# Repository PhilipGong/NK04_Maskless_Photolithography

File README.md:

# NK04_Maskless_Photolithography
Project repository for developing an LCOS based maskless photolithography process.

---
## Objective
To develope an optical setup which is able to:
- Achieve <= 1um feature size
- Ability to expose photoresists at wavelength (405nm / 465nm)
- (Optional) Step the substrate for wafer stepping
- (Optional) Make use of the phase-shift ability of LCOS for phase shift masking

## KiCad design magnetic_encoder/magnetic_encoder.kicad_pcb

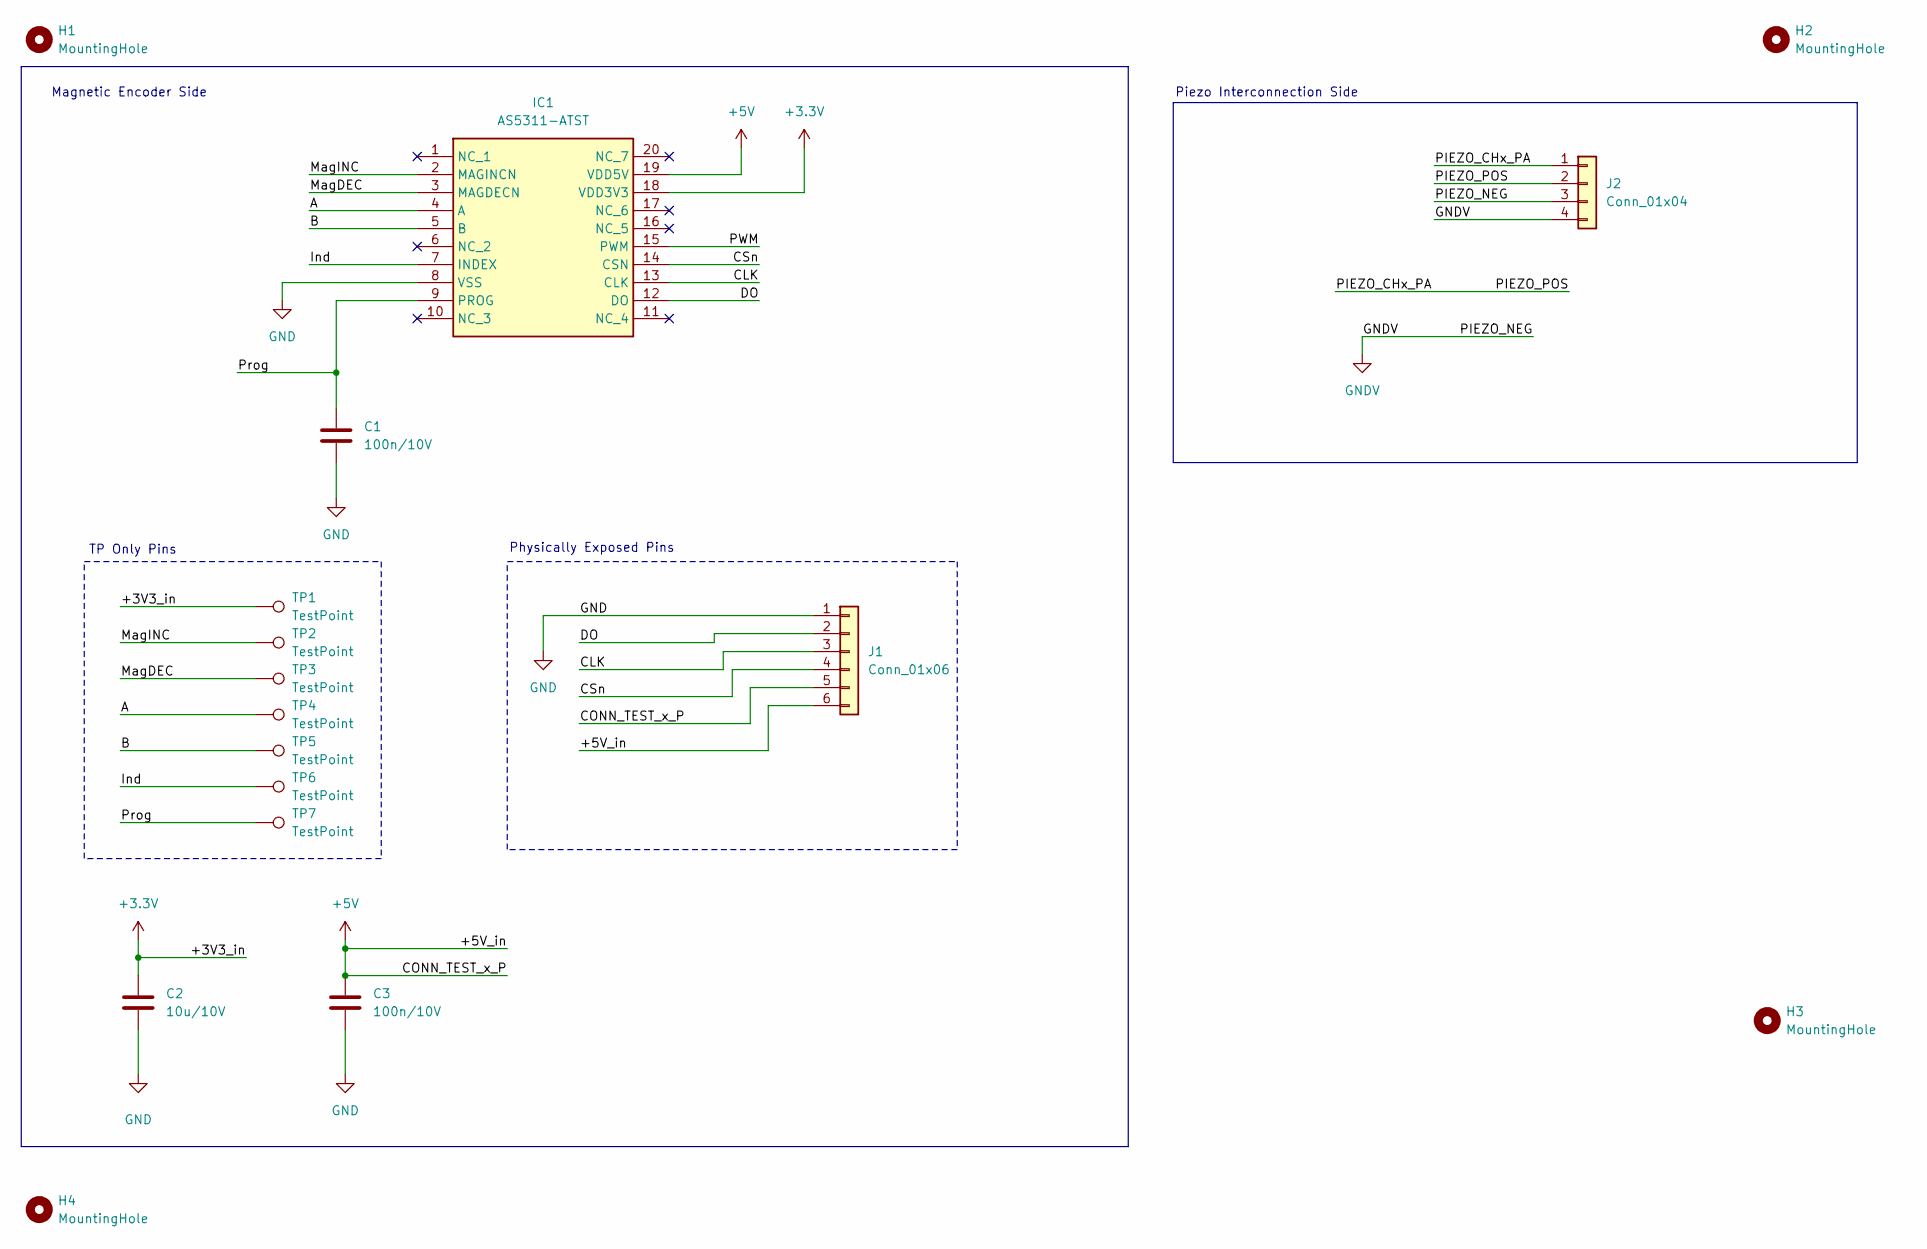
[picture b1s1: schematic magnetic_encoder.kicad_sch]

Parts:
C1, C3: 100n/10V; C_0805_2012Metric
C2: 10u/10V; C_0805_2012Metric
H1, H2, H3, H4: MountingHole; MountingHole_3.2mm_M3
IC1: AS5311-ATST; SOP65P640X120-20N; Manufacturer_Part_Number AS5311-ATST; Mouser Part Number 985-AS5311-ATST
J1: Conn_01x06; SolderWire-0.5sqmm_1x06_P4.6mm_D0.9mm_OD2.1mm_Relief
J2: Conn_01x04; SolderWire-0.5sqmm_1x04_P4.6mm_D0.9mm_OD2.1mm_Relief
TP1, TP2, TP3, TP4, TP5, TP6, TP7: TestPoint; TestPoint_Pad_D1.0mm

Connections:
+3.3V: C2.1, IC1.18 (VDD3V3), TP1.1
+5V: C3.1, IC1.19 (VDD5V), J1.5, J1.6
/A: IC1.4 (A), TP4.1
/B: IC1.5 (B), TP5.1
/CLK: IC1.13 (CLK), J1.3
/CSn: IC1.14 (CSN), J1.4
/DO: IC1.12 (DO), J1.2
/Ind: IC1.7 (INDEX), TP6.1
/MagDEC: IC1.3 (MAGDECN), TP3.1
/MagINC: IC1.2 (MAGINCN), TP2.1
/PIEZO_CHx_PA: J2.1, J2.2
/PWM: IC1.15 (PWM)
/Prog: C1.1, IC1.9 (PROG), TP7.1
GND: C1.2, C2.2, C3.2, IC1.8 (VSS), J1.1
GNDV: J2.3, J2.4

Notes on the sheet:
Physically Exposed Pins
Piezo Interconnection Side
Magnetic Encoder Side
TP Only Pins

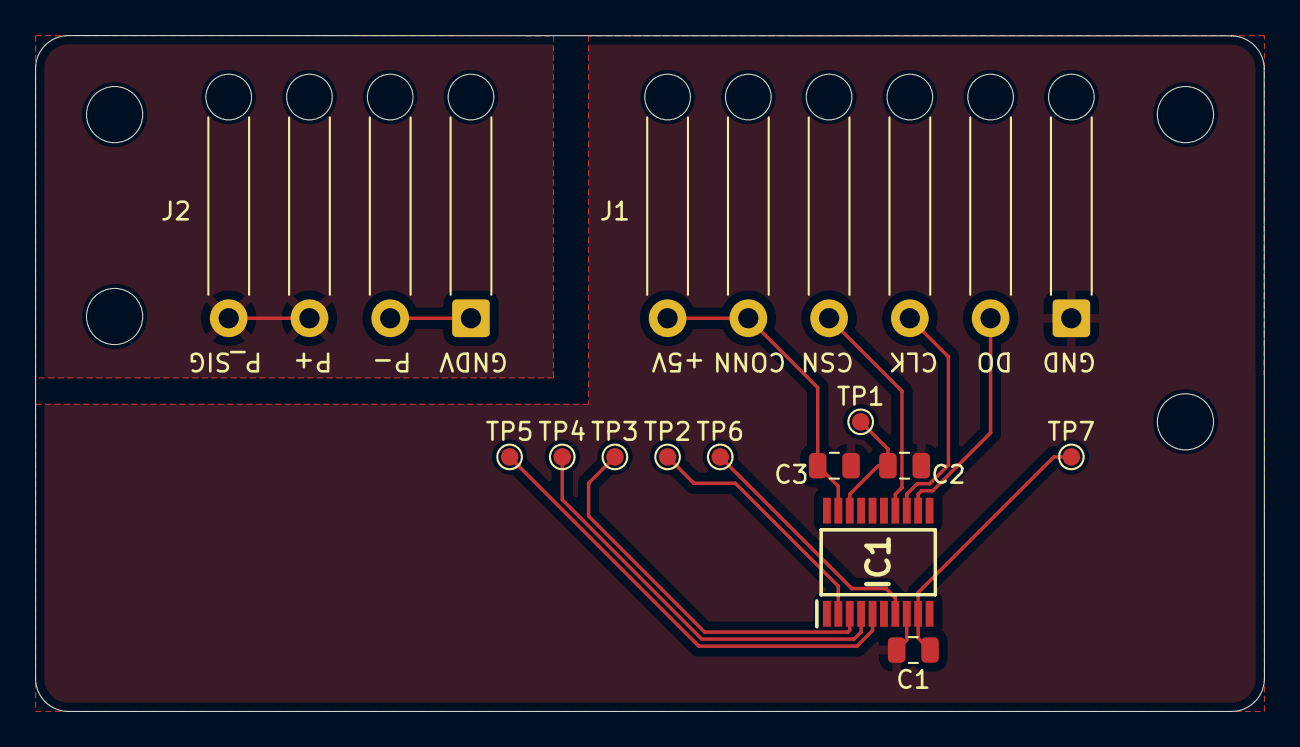
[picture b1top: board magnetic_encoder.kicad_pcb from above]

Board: 2 copper layers, 70.0 x 38.5 mm, 17 parts (0 on the bottom side), 14 nets.

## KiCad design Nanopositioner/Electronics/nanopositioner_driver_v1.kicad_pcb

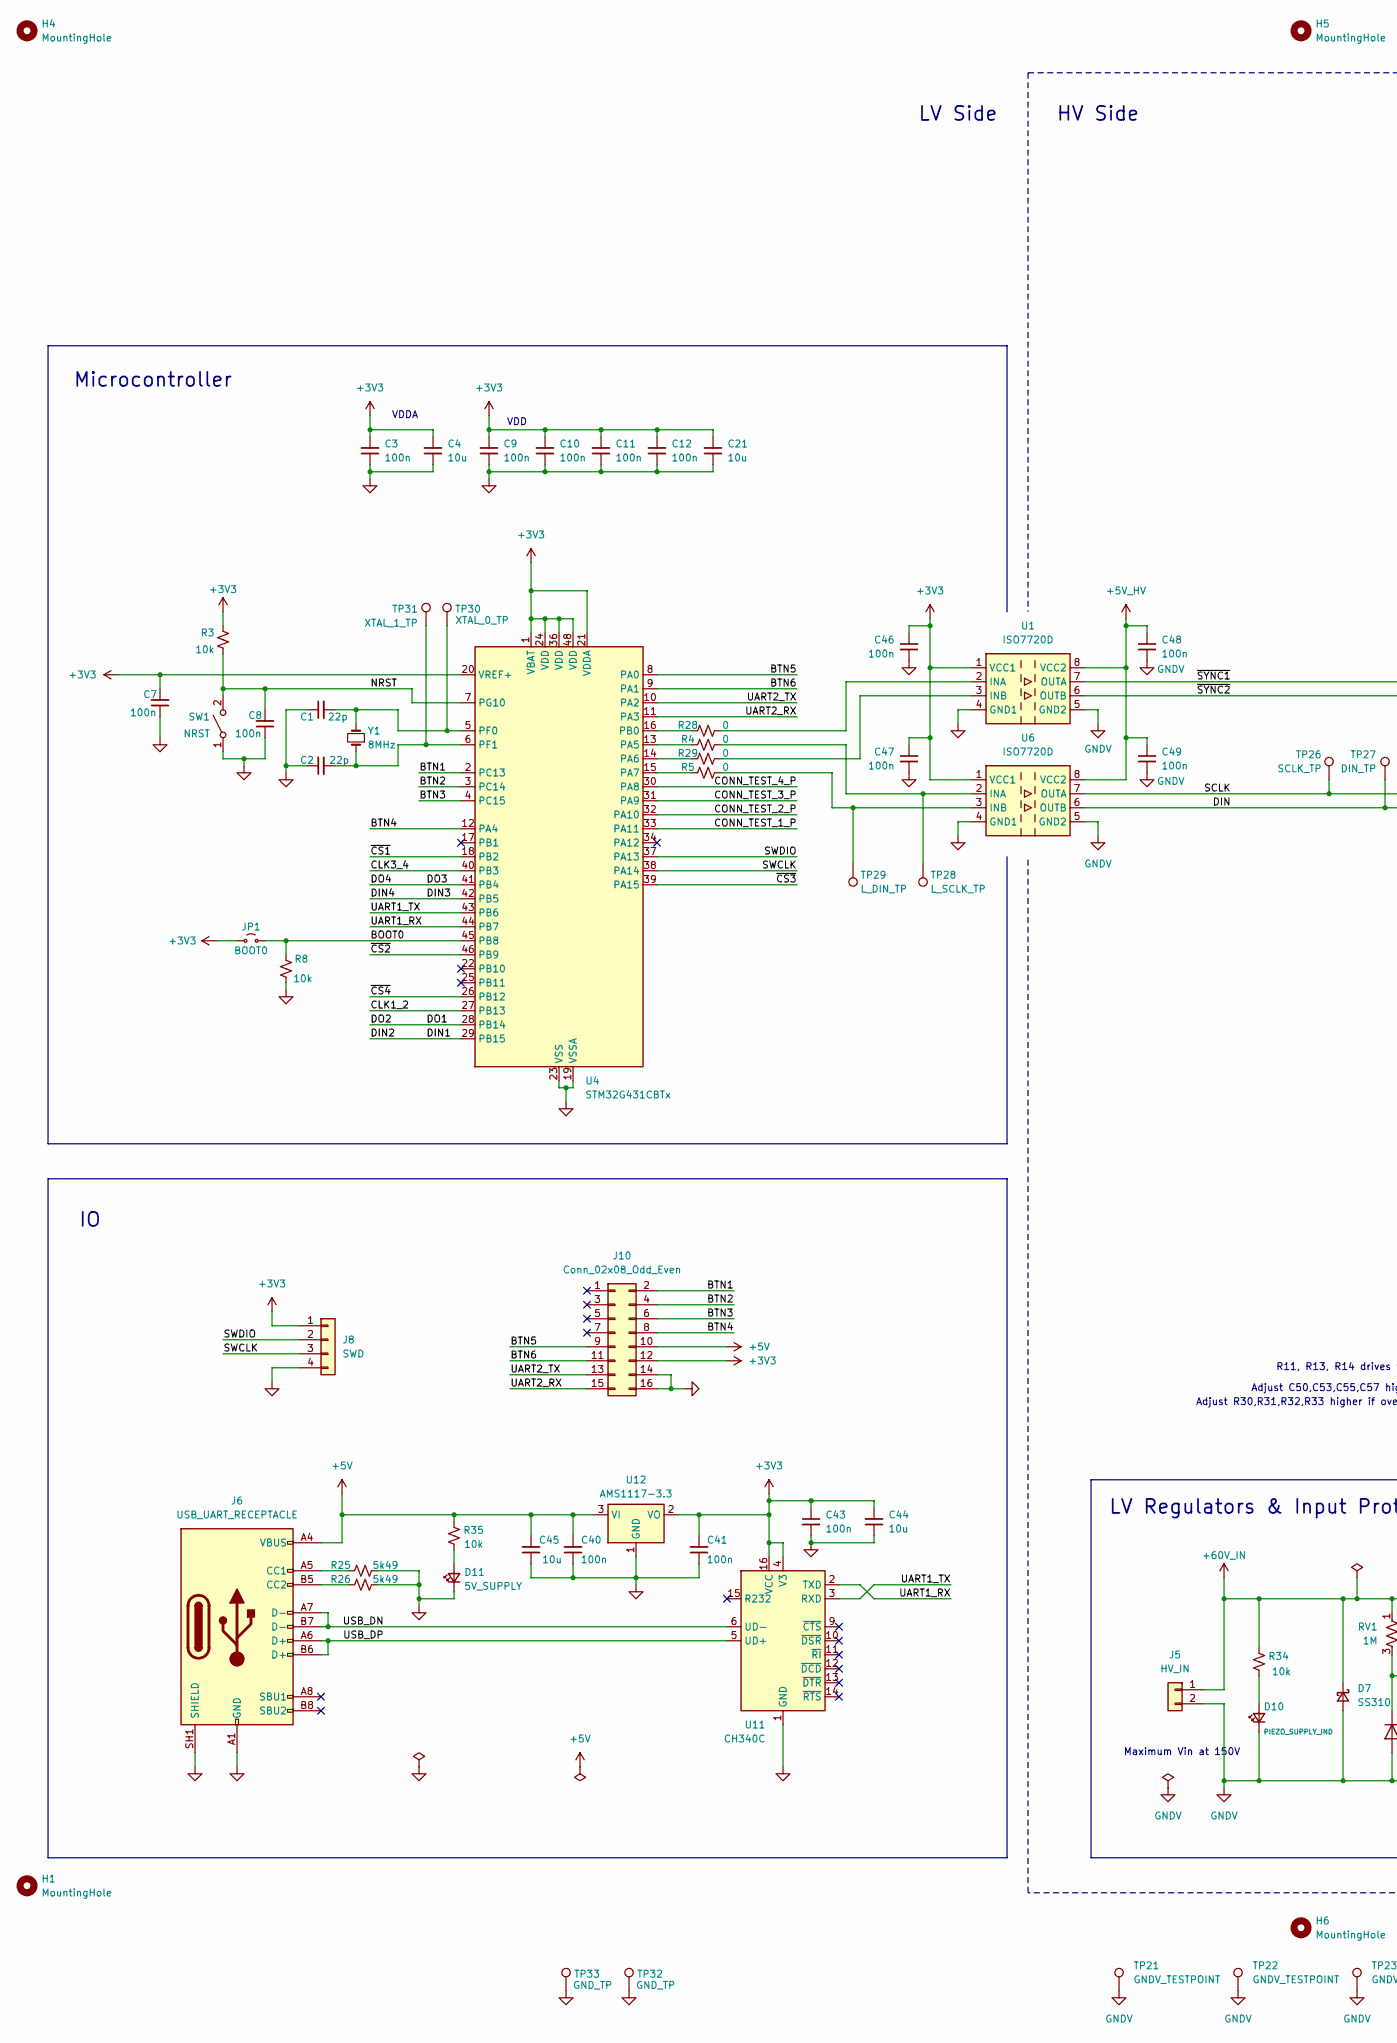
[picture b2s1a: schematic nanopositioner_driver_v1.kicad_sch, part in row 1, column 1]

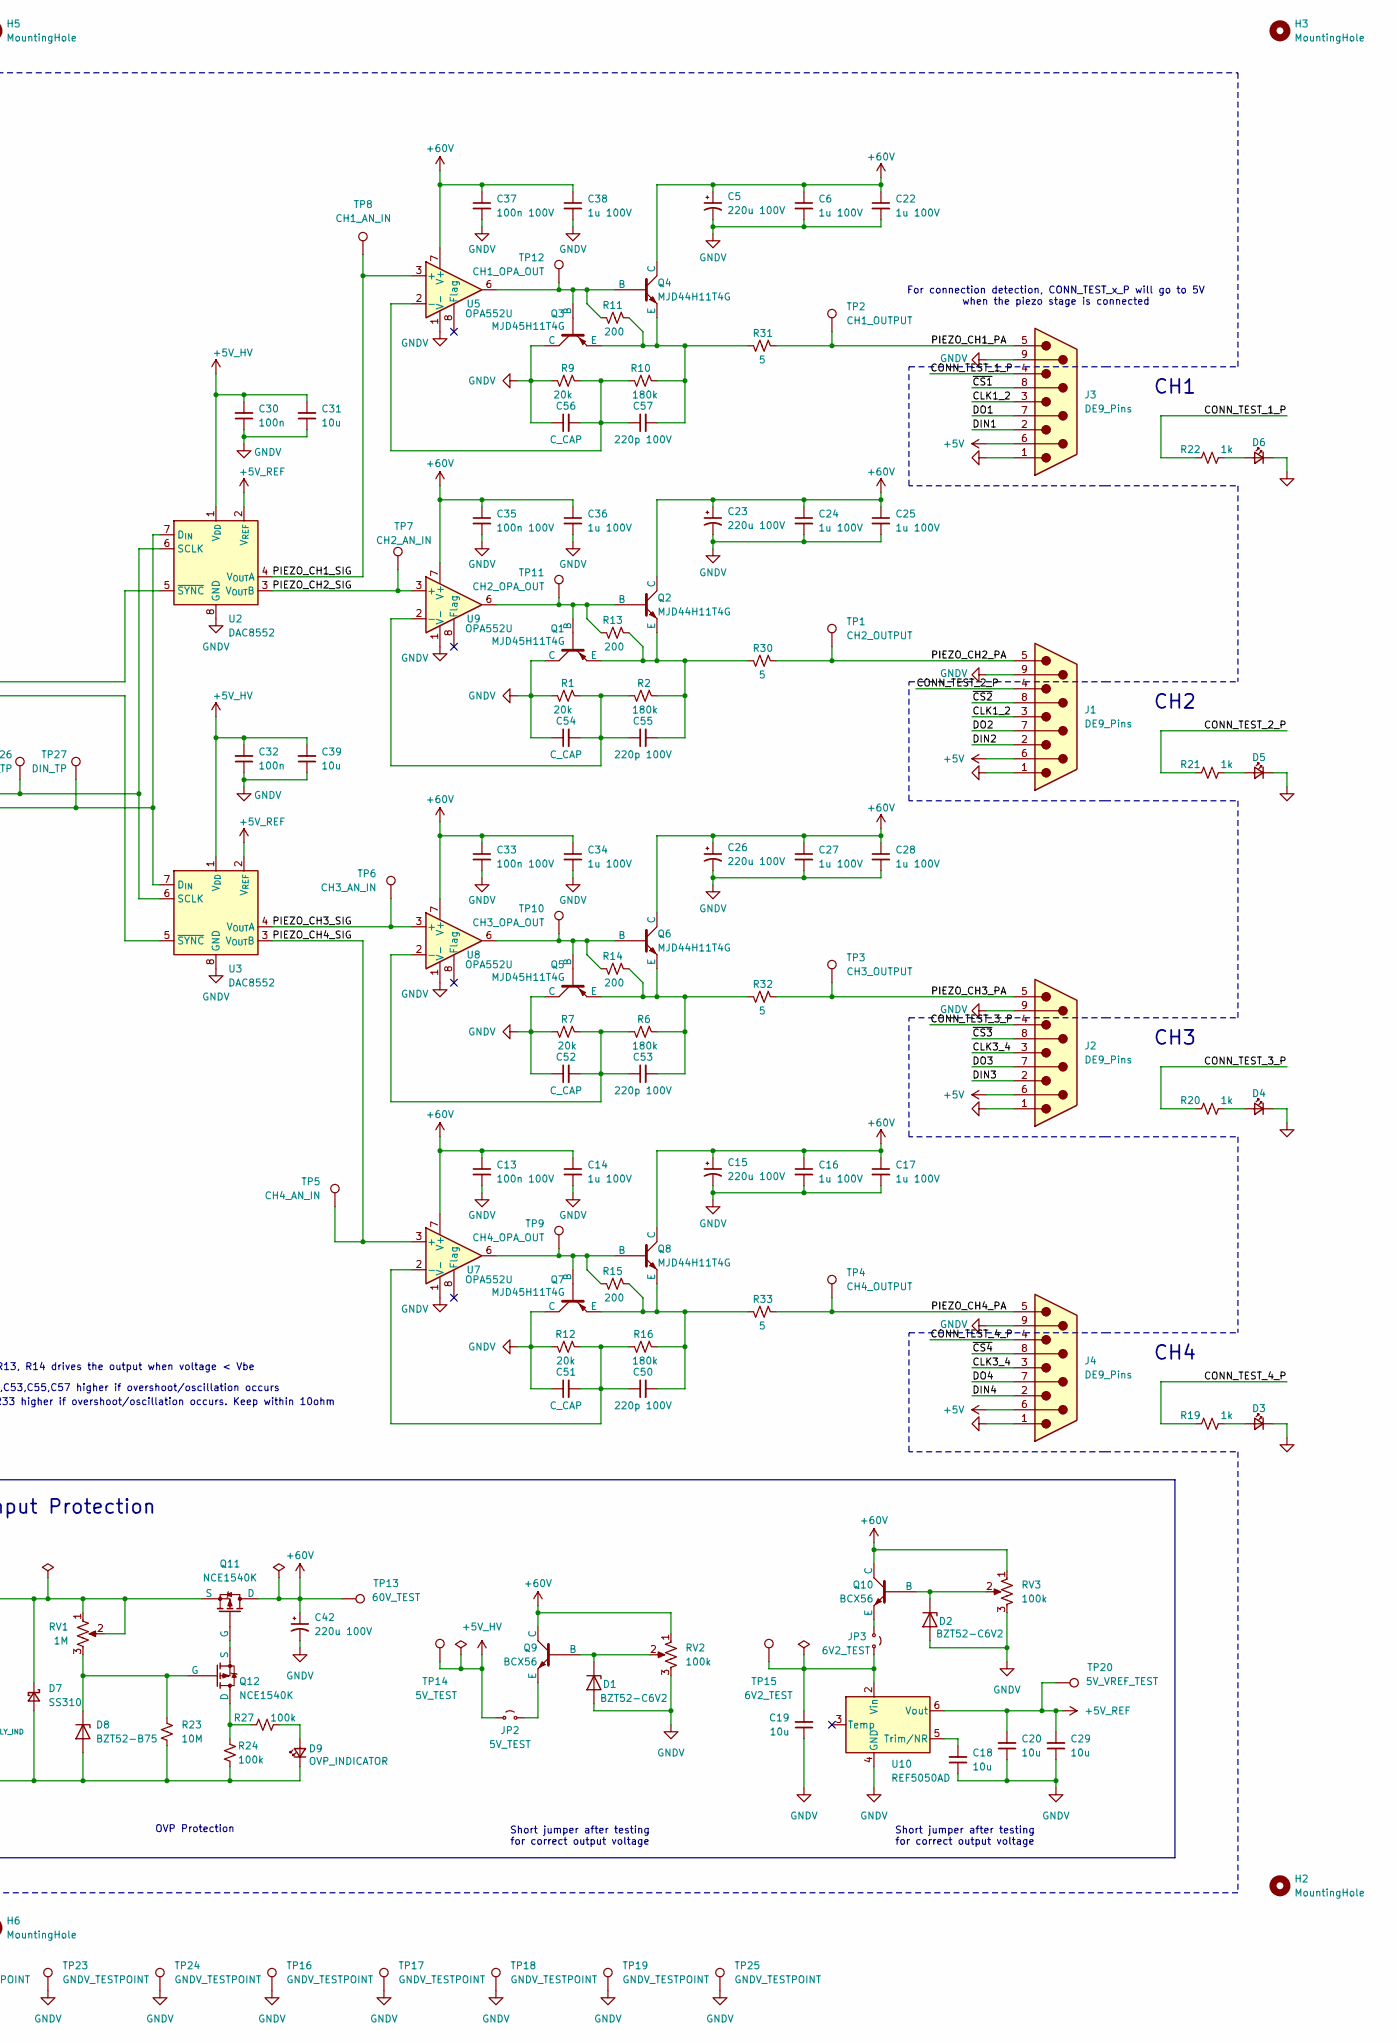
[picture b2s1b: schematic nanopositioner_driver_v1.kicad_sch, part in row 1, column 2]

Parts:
C1, C2: 22p; C_0603_1608Metric
C3, C7, C8, C9, C10, C11, C12, C30, C32, C40, C41, C43, C46, C47, C48, C49: 100n; C_0805_2012Metric
C4, C18, C19, C20, C21, C29, C31, C39, C44, C45: 10u; C_0805_2012Metric
C5, C15, C23, C26, C42: 220u 100V; CP_Radial_D13.0mm_P5.00mm
C6, C14, C16, C17, C22, C24, C25, C27, C28, C34, C36, C38: 1u 100V; C_1206_3216Metric
C13, C33, C35, C37: 100n 100V; C_0805_2012Metric
C50, C53, C55, C57: 220p 100V; C_1206_3216Metric
C51, C52, C54, C56: C_CAP; C_0805_2012Metric
D1, D2: BZT52-C6V2; D_SOD-123F
D3, D4, D5, D6: LED_Small; JST_XH_B2B-XH-A_1x02_P2.50mm_Vertical
D7: SS310; D_SMB
D8: BZT52-B75; D_SOD-123F
D9: OVP_INDICATOR; JST_XH_B2B-XH-A_1x02_P2.50mm_Vertical
D10: PIEZO_SUPPLY_IND; JST_XH_B2B-XH-A_1x02_P2.50mm_Vertical
D11: 5V_SUPPLY; JST_XH_B2B-XH-A_1x02_P2.50mm_Vertical
H1, H2, H3, H4, H5, H6: MountingHole; MountingHole_3.2mm_M3
J1, J2, J3, J4: DE9_Pins; DSUB-9_Socket_Horizontal_P2.77x2.84mm_EdgePinOffset7.70mm_H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
J5: HV_IN; TerminalBlock_bornier-2_P5.08mm
J6: USB_UART_RECEPTACLE; GCT_USB4105GFA120
J8: SWD; PinSocket_1x04_P2.54mm_Vertical
J10: Conn_02x08_Odd_Even; PinHeader_2x08_P2.54mm_Vertical
JP1: BOOT0; PinHeader_1x02_P2.54mm_Vertical
JP2: 5V_TEST; SolderJumper-2_P1.3mm_Open_Pad1.0x1.5mm
JP3: 6V2_TEST; SolderJumper-2_P1.3mm_Open_Pad1.0x1.5mm
Q1, Q3, Q5, Q7: MJD45H11T4G; MJD45H11AJ
Q2, Q4, Q6, Q8: MJD44H11T4G; MJD44H11AJ
Q9, Q10: BCX56; SOT-89-3
Q11, Q12: NCE1540K; TO-252-2
R1, R7, R9, R12: 20k; R_0805_2012Metric
R2, R6, R10, R16: 180k; R_0805_2012Metric
R3, R8, R34, R35: 10k; R_0805_2012Metric
R4, R5, R28, R29: 0; R_0805_2012Metric
R11, R13, R14, R15: 200; R_0805_2012Metric
R19, R20, R21, R22: 1k; R_0805_2012Metric
R23: 10M; R_0805_2012Metric
R24, R27: 100k; R_0805_2012Metric
R25, R26: 5k49; R_0805_2012Metric
R30, R31, R32, R33: 5; R_0805_2012Metric
RV1: 1M; Potentiometer_Bourns_3266W_Vertical
RV2, RV3: 100k; Potentiometer_Bourns_3266W_Vertical
SW1: NRST; TL3342F260QG
TP1: CH2_OUTPUT; TestPoint_Pad_D1.0mm
TP2: CH1_OUTPUT; TestPoint_Pad_D1.0mm
TP3: CH3_OUTPUT; TestPoint_Pad_D1.0mm
TP4: CH4_OUTPUT; TestPoint_Pad_D1.0mm
TP5: CH4_AN_IN; TestPoint_Pad_D1.0mm
TP6: CH3_AN_IN; TestPoint_Pad_D1.0mm
TP7: CH2_AN_IN; TestPoint_Pad_D1.0mm
TP8: CH1_AN_IN; TestPoint_Pad_D1.0mm
TP9: CH4_OPA_OUT; TestPoint_Pad_D1.0mm
TP10: CH3_OPA_OUT; TestPoint_Pad_D1.0mm
TP11: CH2_OPA_OUT; TestPoint_Pad_D1.0mm
TP12: CH1_OPA_OUT; TestPoint_Pad_D1.0mm
TP13: 60V_TEST; TestPoint_Pad_D1.0mm
TP14: 5V_TEST; TestPoint_Pad_D1.0mm
TP15: 6V2_TEST; TestPoint_Pad_D1.0mm
TP16, TP17, TP18, TP19, TP21, TP22, TP23, TP24, TP25: GNDV_TESTPOINT; TestPoint_Pad_D1.0mm
TP20: 5V_VREF_TEST; TestPoint_Pad_D1.0mm
TP26: SCLK_TP; TestPoint_Pad_D1.0mm
TP27: DIN_TP; TestPoint_Pad_D1.0mm
TP28: L_SCLK_TP; TestPoint_Pad_D1.0mm
TP29: L_DIN_TP; TestPoint_Pad_D1.0mm
TP30: XTAL_0_TP; TestPoint_Pad_D1.0mm
TP31: XTAL_1_TP; TestPoint_Pad_D1.0mm
TP32, TP33: GND_TP; TestPoint_Pad_D1.0mm
U1, U6: ISO7720D; SOIC-8_3.9x4.9mm_P1.27mm
U2, U3: DAC8552; Texas_S-PDSO-G8_3x3mm_P0.65mm
U4: STM32G431CBTx; LQFP-48_7x7mm_P0.5mm
U5, U7, U8, U9: OPA552U; SOIC-8_3.9x4.9mm_P1.27mm
U10: REF5050AD; SOIC-8_3.9x4.9mm_P1.27mm
U11: CH340C; SOIC-16_3.9x9.9mm_P1.27mm
U12: AMS1117-3.3; SOT-223-3_TabPin2
Y1: 8MHz; YSX530

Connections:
+3V3: C3.2, C4.2, C7.2, C9.2, C10.2, C11.2, C12.2, C21.2, C41.2, C43.1, C44.2, C46.1, C47.1, J8.1, J10.12, JP1.1 (A), R3.2, U1.1 (VCC1), U4.1 (VBAT), U4.20 (VREF+), U4.21 (VDDA), U4.24 (VDD), U4.36 (VDD), U4.48 (VDD), U6.1 (VCC1), U11.4 (V3), U11.16 (VCC), U12.2 (VO)
+5V: C40.2, C45.2, J1.6, J2.6, J3.6, J4.6, J6.A4 (VBUS), J6.A9 (VBUS), J6.B4 (VBUS), J6.B9 (VBUS), J10.10, R35.1, U12.3 (VI)
+5V_HV: C30.2, C31.2, C32.2, C39.2, C48.1, C49.1, JP2.1 (A), TP14.1, U1.8 (VCC2), U2.1 (V_{DD}), U3.1 (V_{DD}), U6.8 (VCC2)
+5V_REF: C20.2, C29.2, TP20.1, U2.2 (V_{REF}), U3.2 (V_{REF}), U10.6 (Vout)
+60V: C5.1, C6.1, C13.1, C14.1, C15.1, C16.1, C17.1, C22.1, C23.1, C24.1, C25.1, C26.1, C27.1, C28.1, C33.1, C34.1, C35.1, C36.1, C37.1, C38.1, C42.1, Q2.2 (C), Q4.2 (C), Q6.2 (C), Q8.2 (C), Q9.2 (C), Q10.2 (C), Q11.2 (D), RV2.1, RV3.1, TP13.1, U5.7 (V+), U7.7 (V+), U8.7 (V+), U9.7 (V+)
+60V_IN: D7.1 (K), J5.1, Q11.3 (S), R34.1, RV1.1, RV1.2
/BOOT0: JP1.2 (B), R8.1, U4.45 (PB8)
/BTN1: J10.2, U4.2 (PC13)
/BTN2: J10.4, U4.3 (PC14)
/BTN3: J10.6, U4.4 (PC15)
/BTN4: J10.8, U4.12 (PA4)
/BTN5: J10.9, U4.8 (PA0)
/BTN6: J10.11, U4.9 (PA1)
/CLK1_2: J1.3, J3.3, U4.27 (PB13)
/CLK3_4: J2.3, J4.3, U4.40 (PB3)
/CONN_TEST_1_P: J3.4, R22.1, U4.33 (PA11)
/CONN_TEST_2_P: J1.4, R21.1, U4.32 (PA10)
/CONN_TEST_3_P: J2.4, R20.1, U4.31 (PA9)
/CONN_TEST_4_P: J4.4, R19.1, U4.30 (PA8)
/DIN: TP27.1, U2.7 (D_{IN}), U3.7 (D_{IN}), U6.6 (OUTB)
/DIN1: J1.2, J3.2, U4.29 (PB15)
/DIN3: J2.2, J4.2, U4.42 (PB5)
/DO1: J1.7, J3.7, U4.28 (PB14)
/DO3: J2.7, J4.7, U4.41 (PB4)
/NRST: C8.2, R3.1, SW1.2 (B), U4.7 (PG10)
/PIEZO_CH1_PA: J3.5, R31.1, TP2.1
/PIEZO_CH1_SIG: TP8.1, U2.4 (V_{OUT}A), U5.3 (+)
/PIEZO_CH2_PA: J1.5, R30.1, TP1.1
/PIEZO_CH2_SIG: TP7.1, U2.3 (V_{OUT}B), U9.3 (+)
/PIEZO_CH3_PA: J2.5, R32.1, TP3.1
/PIEZO_CH3_SIG: TP6.1, U3.4 (V_{OUT}A), U8.3 (+)
/PIEZO_CH4_PA: J4.5, R33.1, TP4.1
/PIEZO_CH4_SIG: TP5.1, U3.3 (V_{OUT}B), U7.3 (+)
/SCLK: TP26.1, U2.6 (SCLK), U3.6 (SCLK), U6.7 (OUTA)
/SWCLK: J8.3, U4.38 (PA14)
/SWDIO: J8.2, U4.37 (PA13)
/UART1_RX: U4.44 (PB7), U11.2 (TXD)
/UART1_TX: U4.43 (PB6), U11.3 (RXD)
/UART2_RX: J10.15, U4.11 (PA3)
/UART2_TX: J10.13, U4.10 (PA2)
/USB_DN: J6.A7 (D-), J6.B7 (D-), U11.6 (UD-)
/USB_DP: J6.A6 (D+), J6.B6 (D+), U11.5 (UD+)
/~CS1: J3.8, U4.18 (PB2)
/~CS2: J1.8, U4.46 (PB9)
/~CS3: J2.8, U4.39 (PA15)
/~CS4: J4.8, U4.26 (PB12)
/~SYNC1: U1.7 (OUTA), U2.5 (~SYNC)
/~SYNC2: U1.6 (OUTB), U3.5 (~SYNC)
GND: C1.1, C2.1, C3.1, C4.1, C7.1, C8.1, C9.1, C10.1, C11.1, C12.1, C21.1, C40.1, C41.1, C43.2, C44.1, C45.1, C46.2, C47.2, D3.1 (K), D4.1 (K), D5.1 (K), D6.1 (K), D11.1 (K), J1.1, J2.1, J3.1, J4.1, J6.A1 (GND), J6.A12 (GND), J6.B1 (GND), J6.B12 (GND), J6.SH1 (SHIELD), J6.SH2 (SHIELD), J6.SH3 (SHIELD), J6.SH4 (SHIELD), J8.4, J10.14, J10.16, R8.2, R25.1, R26.1, SW1.1 (A), TP32.1, TP33.1, U1.4 (GND1), U4.19 (VSSA), U4.23 (VSS), U4.35 (VSS), U4.47 (VSS), U6.4 (GND1), U11.1 (GND), U12.1 (GND)
GNDV: C5.2, C6.2, C13.2, C14.2, C15.2, C16.2, C17.2, C18.1, C19.1, C20.1, C22.2, C23.2, C24.2, C25.2, C26.2, C27.2, C28.2, C29.1, C30.1, C31.1, C32.1, C33.2, C34.2, C35.2, C36.2, C37.2, C38.2, C39.1, C42.2, C48.2, C49.2, C51.1, C52.1, C54.1, C56.1, D1.2 (A), D2.2 (A), D7.2 (A), D8.2 (A), D9.1 (K), D10.1 (K), J1.9, J2.9, J3.9, J4.9, J5.2, Q1.2 (C), Q3.2 (C), Q5.2 (C), Q7.2 (C), R1.2, R7.2, R9.2, R12.2, R23.2, R24.1, RV2.3, RV3.3, TP16.1, TP17.1, TP18.1, TP19.1, TP21.1, TP22.1, TP23.1, TP24.1, TP25.1, U1.5 (GND2), U2.8 (GND), U3.8 (GND), U5.1 (V-), U5.4 (V-), U5.5 (V-), U6.5 (GND2), U7.1 (V-), U7.4 (V-), U7.5 (V-), U8.1 (V-), U8.4 (V-), U8.5 (V-), U9.1 (V-), U9.4 (V-), U9.5 (V-), U10.4 (GND)
unnamed: D1.1 (K), Q9.3 (B), RV2.2
unnamed: D2.1 (K), Q10.3 (B), RV3.2
unnamed: D3.2 (A), R19.2
unnamed: D4.2 (A), R20.2
unnamed: D5.2 (A), R21.2
unnamed: D6.2 (A), R22.2
unnamed: D8.1 (K), Q12.1 (G), R23.1, RV1.3
unnamed: D9.2 (A), R27.1
unnamed: D10.2 (A), R34.2
unnamed: D11.2 (A), R35.2
unnamed: J6.A5 (CC1), R25.2
unnamed: J6.B5 (CC2), R26.2
unnamed: JP2.2 (B), Q9.1 (E)
unnamed: JP3.1 (A), Q10.1 (E)
unnamed: C19.2, JP3.2 (B), TP15.1, U10.2 (Vin)
unnamed: Q1.1 (B), Q2.1 (B), R13.2, TP11.1, U9.6
unnamed: C55.2, Q1.3 (E), Q2.3 (E), R2.1, R13.1, R30.2
unnamed: Q3.1 (B), Q4.1 (B), R11.2, TP12.1, U5.6
unnamed: C57.2, Q3.3 (E), Q4.3 (E), R10.1, R11.1, R31.2
unnamed: Q5.1 (B), Q6.1 (B), R14.2, TP10.1, U8.6
unnamed: C53.2, Q5.3 (E), Q6.3 (E), R6.1, R14.1, R32.2
unnamed: Q7.1 (B), Q8.1 (B), R15.2, TP9.1, U7.6
unnamed: C50.2, Q7.3 (E), Q8.3 (E), R15.1, R16.1, R33.2
unnamed: Q11.1 (G), Q12.3 (S)
unnamed: Q12.2 (D), R24.2, R27.2
unnamed: R28.2, U1.2 (INA)
unnamed: R29.2, U1.3 (INB)
unnamed: R4.1, U4.13 (PA5)
unnamed: R29.1, U4.14 (PA6)
unnamed: R5.1, U4.15 (PA7)
unnamed: R28.1, U4.16 (PB0)
unnamed: C1.2, TP30.1, U4.5 (PF0), Y1.2
unnamed: C2.2, TP31.1, U4.6 (PF1), Y1.1
unnamed: C56.2, C57.1, R9.1, R10.2, U5.2 (-)
unnamed: R4.2, TP28.1, U6.2 (INA)
unnamed: R5.2, TP29.1, U6.3 (INB)
unnamed: C50.1, C51.2, R12.1, R16.2, U7.2 (-)
unnamed: C52.2, C53.1, R6.2, R7.1, U8.2 (-)
unnamed: C54.2, C55.1, R1.1, R2.2, U9.2 (-)
unnamed: C18.2, U10.5 (Trim/NR)

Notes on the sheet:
Short jumper after testing for correct output voltage
OVP Protection
CH1
HV Side
LV Regulators & Input Protection
Adjust C50,C53,C55,C57 higher if overshoot/oscillation occurs
VDDA
Microcontroller
VDD
Maximum Vin at 150V
R11, R13, R14 drives the output when voltage < Vbe
CH3
CH2
LV Side
For connection detection, CONN_TEST_x_P will go to 5V when the piezo stage is connected
Adjust R30,R31,R32,R33 higher if overshoot/oscillation occurs. Keep within 10ohm
CH4

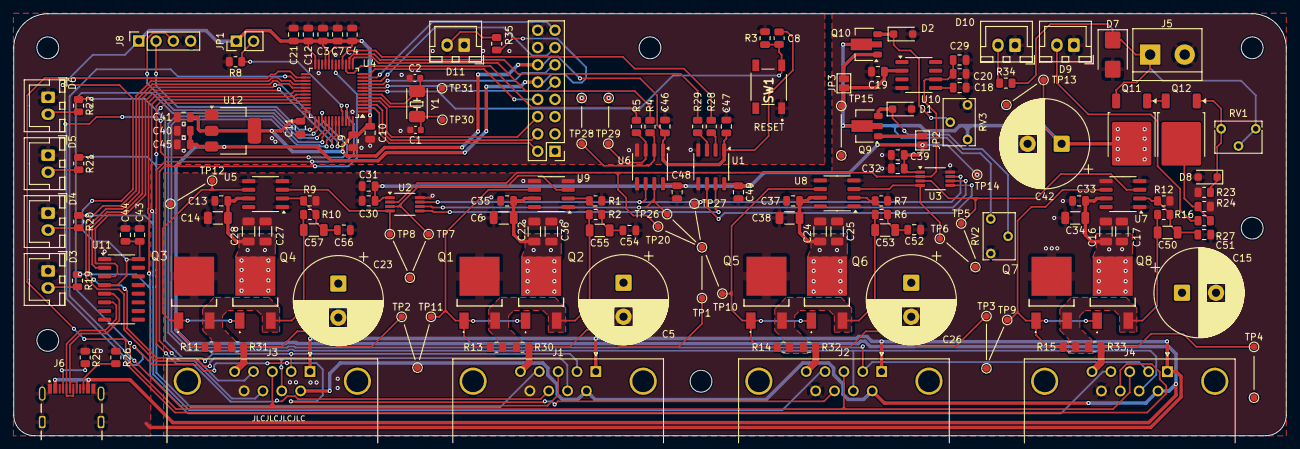
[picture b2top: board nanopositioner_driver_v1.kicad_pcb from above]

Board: 2 copper layers, 187.0 x 62.0 mm, 180 parts (0 on the bottom side), 90 nets.

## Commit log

2025-09-05 Added related literatures
2025-09-05 Updated shopping list
2025-09-06 Added literature for using immersion objective
    Provided the method of using a coverslip over the photoresist and use water as immersion fluid
2025-11-14 Design of nanopositioner driver
2025-11-22 Updated the design of the mainboard
2025-11-22 Updated design of the mainboard
2025-12-05 Updated driver design
2025-12-05 PDF of the schematic design
2026-01-01 Updated the complete PCB design
2026-01-02 magnetic encoder sch+layout
2026-01-06 updated unused pins into testpoints
2026-01-16 Added some markings and solved thermal relief related DRC
